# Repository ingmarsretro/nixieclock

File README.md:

# nixieclock
it is a project for a simple nixieclock hardware and software design based on atmega 8bit controller

develpment environment for this project below:
- Arduino IDE 
- Autodesk Eagle schematic and layout tool for pcb design

all files are hosted here in these folders

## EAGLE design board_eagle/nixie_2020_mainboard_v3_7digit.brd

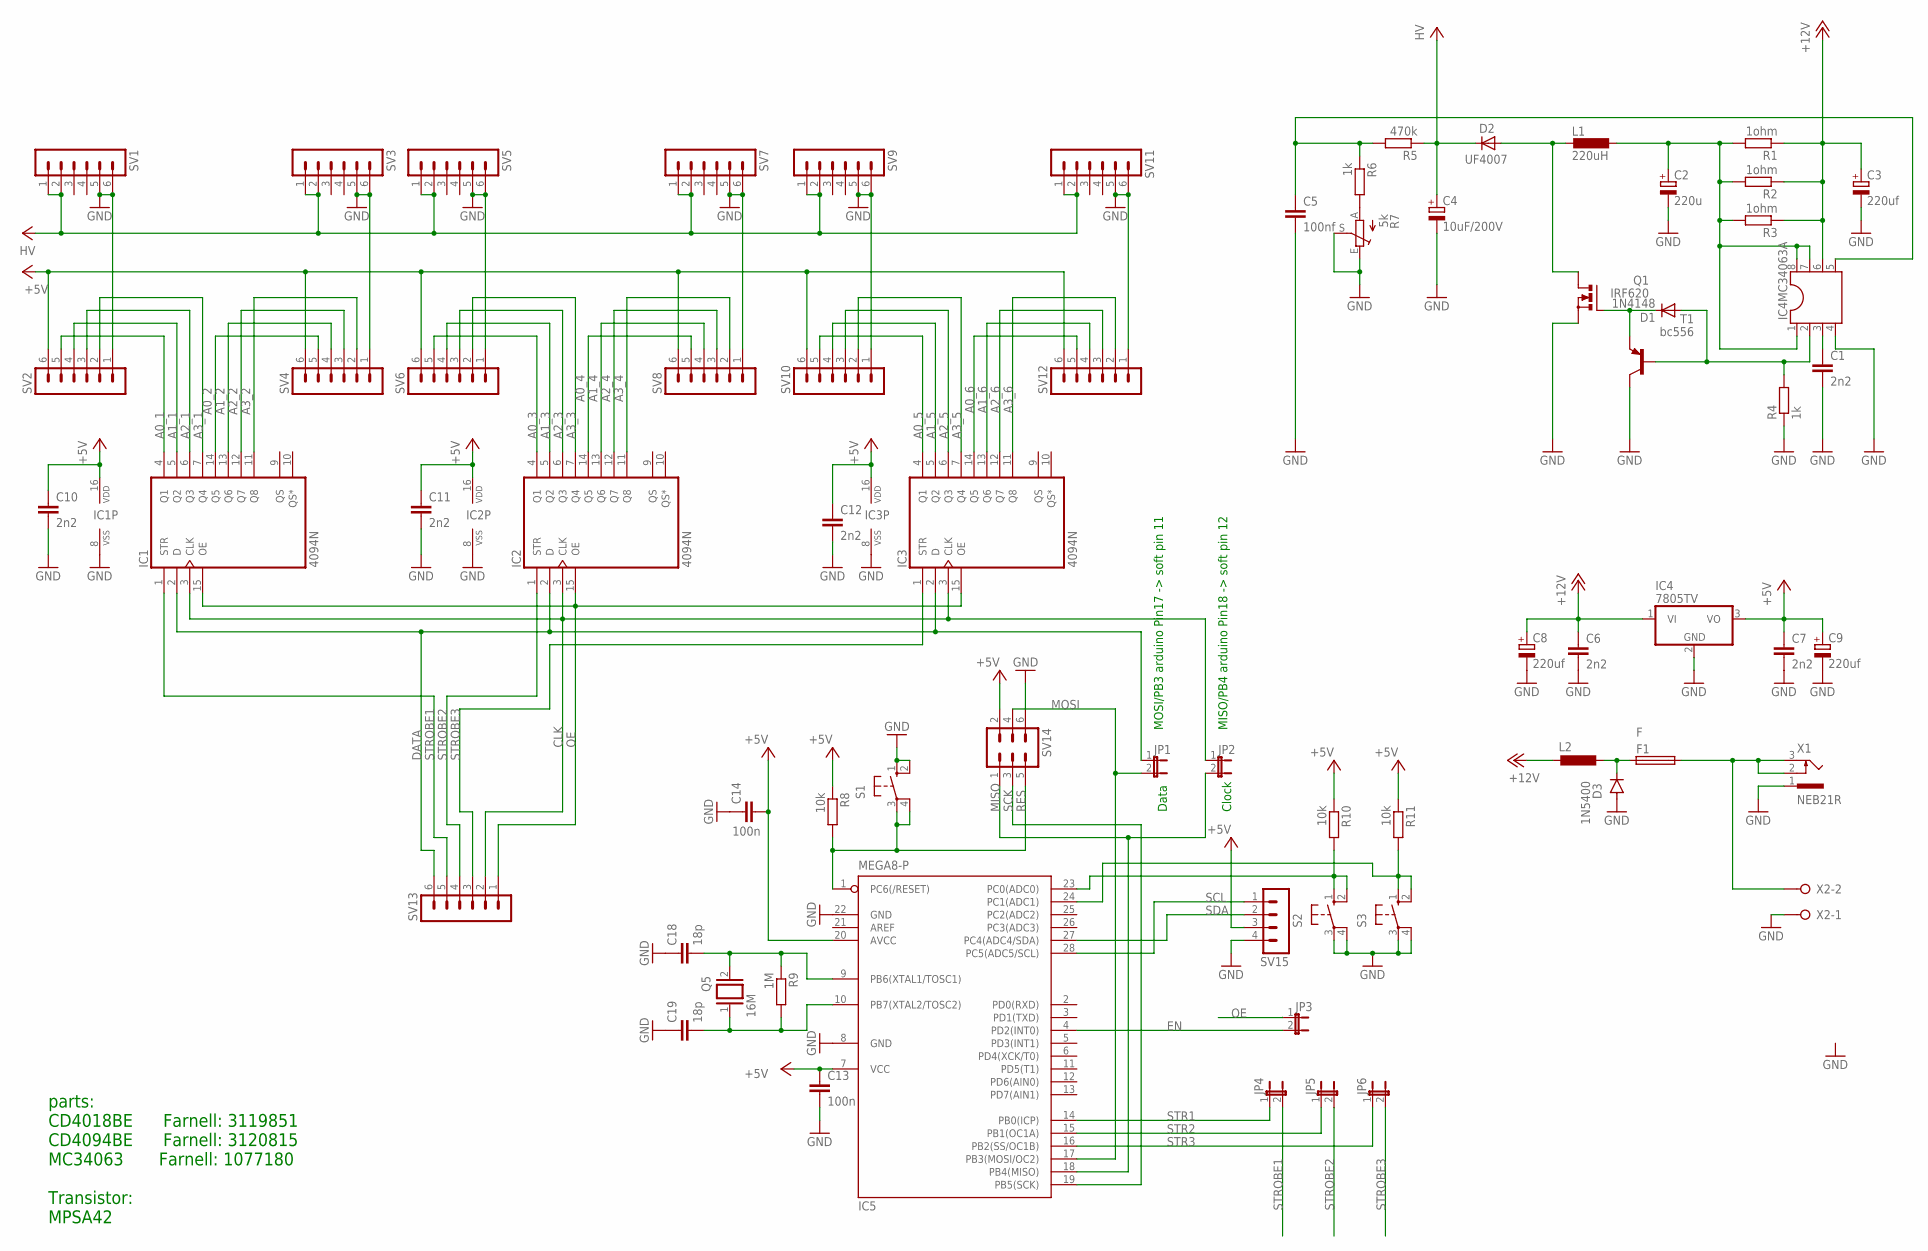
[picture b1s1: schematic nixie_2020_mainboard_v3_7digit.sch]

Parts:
C1, C6, C7, C10, C11, C12: 2n2; C050-030X075
C2: 220u; E5-10,5
C3, C8, C9: 220uf; E5-10,5
C4: 10uF/200V; E5-10,5
C5: 100nf; C075-042X103
C13, C14: 100n; C050-025X075
C18, C19: 18p; C050-025X075
D1: 1N4148; DO35-10
D2: UF4007; DO35-10
D3: 1N5400; DO201-15
F1: F; SHK20L
IC1, IC2, IC3: 4094N; DIL16
IC4: 7805TV; TO220V
IC4MC34063A: DIL8S; SOCKET-08
IC5: MEGA8-P; DIL28-3
JP1, JP2, JP3, JP4, JP5, JP6: JP1E; JP1
L1: 220uH; LAN02KR
L2: L-EU0207/10; 0207/10
Q1: IRF620; TO220BV
Q5: 16M; QS
R1, R2, R3: 1ohm; 0207/12
R4, R6: 1k; 0207/12
R5: 470k; 0207/12
R7: 5k; RJ9W
R8, R10, R11: 10k; 0207/12
R9: 1M; 0207/12
S1, S2, S3: 10-XX; B3F-10XX
SV1, SV2, SV3, SV4, SV5, SV6, SV7, SV8, SV9, SV10, SV11, SV12, SV13: MA06-1
SV14: MA03-2
SV15: MA04-1
T1: bc556; TO92-EBC
X1: NEB21R
X2: W237-02P; W237-132

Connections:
+5V: C7.1, C9.+, C10.1, C11.1, C12.1, C13.1, C14.2, IC1.16 (VDD), IC2.16 (VDD), IC3.16 (VDD), IC4.3 (VO), IC5.7 (VCC), IC5.20 (AVCC), R8.1, R10.1, R11.1, SV2.6, SV4.6, SV6.6, SV8.6, SV10.6, SV12.6, SV14.2, SV15.3
+12V: C3.+, C6.1, C8.+, IC4.1 (VI), IC4MC34063A.6, L2.1, R1.1, R2.1, R3.1
A0_1: IC1.4 (Q1), SV2.5
A0_2: IC1.14 (Q5), SV4.5
A0_3: IC2.4 (Q1), SV6.5
A0_4: IC2.14 (Q5), SV8.5
A0_5: IC3.4 (Q1), SV10.5
A0_6: IC3.14 (Q5), SV12.5
A1_1: IC1.5 (Q2), SV2.4
A1_2: IC1.13 (Q6), SV4.4
A1_3: IC2.5 (Q2), SV6.4
A1_4: IC2.13 (Q6), SV8.4
A1_5: IC3.5 (Q2), SV10.4
A1_6: IC3.13 (Q6), SV12.4
A2_1: IC1.6 (Q3), SV2.3
A2_2: IC1.12 (Q7), SV4.3
A2_3: IC2.6 (Q3), SV6.3
A2_4: IC2.12 (Q7), SV8.3
A2_5: IC3.6 (Q3), SV10.3
A2_6: IC3.12 (Q7), SV12.3
A3_1: IC1.7 (Q4), SV2.2
A3_2: IC1.11 (Q8), SV4.2
A3_3: IC2.7 (Q4), SV6.2
A3_4: IC2.11 (Q8), SV8.2
A3_5: IC3.7 (Q4), SV10.2
A3_6: IC3.11 (Q8), SV12.2
CLK: IC1.3 (CLK), IC2.3 (CLK), IC3.3 (CLK), JP2.1, SV13.2
DATA: IC1.2 (D), IC2.2 (D), IC3.2 (D), JP1.1, SV13.6
EN: IC5.4 (PD2(INT0)), JP3.2
GND: C1.2, C2.-, C3.-, C4.-, C5.2, C6.2, C7.2, C8.-, C9.-, C10.2, C11.2, C12.2, C13.2, C14.1, C18.1, C19.1, D3.A, IC1.8 (VSS), IC2.8 (VSS), IC3.8 (VSS), IC4.2 (GND), IC4MC34063A.4, IC5.8 (GND), IC5.22 (GND), Q1.S, R4.1, R7.E, R7.S, S1.1 (S), S1.2 (S1), S2.3, S2.4 (P1), S3.3, S3.4 (P1), SV1.5, SV1.6, SV2.1, SV3.5, SV3.6, SV4.1, SV5.5, SV5.6, SV6.1, SV7.5, SV7.6, SV8.1, SV9.5, SV9.6, SV10.1, SV11.5, SV11.6, SV12.1, SV14.6, SV15.4, T1.C, X1.1, X2.1
MISO: IC5.18 (PB4(MISO)), JP2.2, SV14.1
MOSI: IC5.17 (PB3(MOSI/OC2)), JP1.2, SV14.4
unnamed: F1.2A (2), X1.2, X1.3, X2.2
unnamed: D3.C, F1.1A (1), L2.2
unnamed: IC5.24 (PC1(ADC1)), R11.2, S3.1 (S), S3.2 (S1)
unnamed: IC5.23 (PC0(ADC0)), R10.2, S2.1 (S), S2.2 (S1)
unnamed: C18.2, IC5.9 (PB6(XTAL1/TOSC1)), Q5.2, R9.1
unnamed: C19.2, IC5.10 (PB7(XTAL2/TOSC2)), Q5.1, R9.2
unnamed: C1.1, IC4MC34063A.3
unnamed: D1.A, IC4MC34063A.2, R4.2, T1.B
unnamed: D1.C, Q1.G, T1.E
unnamed: D2.A, L1.2, Q1.D
unnamed: C2.+, IC4MC34063A.1, IC4MC34063A.7, IC4MC34063A.8, L1.1, R1.2, R2.2, R3.2
unnamed: C5.1, IC4MC34063A.5, R5.2, R6.1
unnamed: R6.2, R7.A
OE: IC1.15 (OE), IC2.15 (OE), IC3.15 (OE), JP3.1, SV13.1
RES: IC5.1 (PC6(/RESET)), R8.2, S1.3, S1.4 (P1), SV14.5
SCK: IC5.19 (PB5(SCK)), SV14.3
SCL: IC5.28 (PC5(ADC5/SCL)), SV15.1
SDA: IC5.27 (PC4(ADC4/SDA)), SV15.2
STR1: IC5.14 (PB0(ICP)), JP4.1
STR2: IC5.15 (PB1(OC1A)), JP5.1
STR3: IC5.16 (PB2(SS/OC1B)), JP6.1
STROBE1: IC1.1 (STR), JP4.2, SV13.5
STROBE2: IC2.1 (STR), JP5.2, SV13.4
STROBE3: IC3.1 (STR), JP6.2, SV13.3
VCC: C4.+, D2.C, R5.1, SV1.1, SV1.2, SV3.1, SV3.2, SV5.1, SV5.2, SV7.1, SV7.2, SV9.1, SV9.2, SV11.1, SV11.2

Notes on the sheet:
MOSI/PB3 arduino Pin17 -> soft pin 11
Data
Clock
MISO/PB4 arduino Pin18 -> soft pin 12
parts: CD4018BE Farnell: 3119851 CD4094BE Farnell: 3120815 MC34063 Farnell: 1077180 Transistor: MPSA42

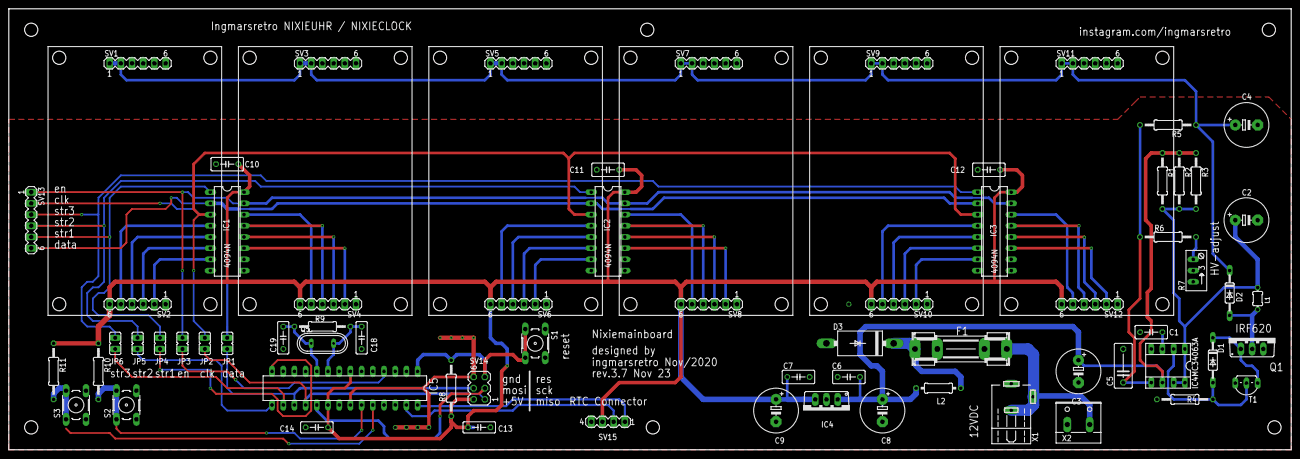
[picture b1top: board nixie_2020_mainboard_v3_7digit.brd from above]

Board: 2 copper layers, 290.8 x 100.0 mm, 68 parts (0 on the bottom side), 57 nets.

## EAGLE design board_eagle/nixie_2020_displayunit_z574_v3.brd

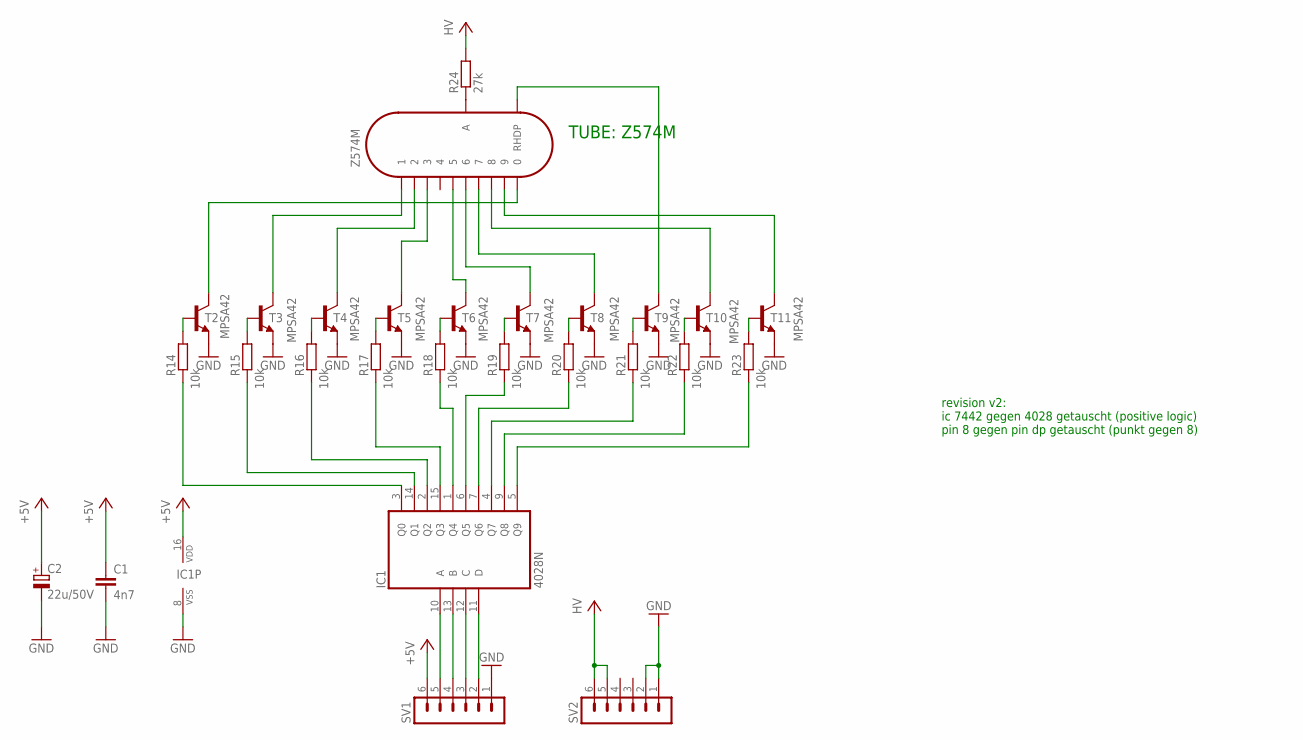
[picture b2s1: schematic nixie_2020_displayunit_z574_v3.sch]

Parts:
C1: 4n7; C075-032X103
C2: 22u/50V; E5-5
IC1: 4028N; DIL16
R14, R15, R16, R17, R18, R19, R20, R21, R22, R23: 10k; 0207/10
R24: 27k; 0207/10
SV1, SV2: MA06-1
T2, T3, T4, T5, T6, T7, T8, T9, T10, T11: MPSA42; TO92-EBC
Z574M: IN-8-2

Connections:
+5V: C1.1, C2.+, IC1.16 (VDD), SV1.6
GND: C1.2, C2.-, IC1.8 (VSS), SV1.1, SV2.1, SV2.2, T2.E, T3.E, T4.E, T5.E, T6.E, T7.E, T8.E, T9.E, T10.E, T11.E
unnamed: IC1.10 (A), SV1.5
unnamed: IC1.13 (B), SV1.4
unnamed: IC1.12 (C), SV1.3
unnamed: IC1.11 (D), SV1.2
unnamed: T9.C, Z574M.. (RHDP)
unnamed: R14.2, T2.B
unnamed: R15.2, T3.B
unnamed: R16.2, T4.B
unnamed: R17.2, T5.B
unnamed: R18.2, T6.B
unnamed: R19.2, T7.B
unnamed: R20.2, T8.B
unnamed: R21.2, T9.B
unnamed: R22.2, T10.B
unnamed: R23.2, T11.B
unnamed: IC1.3 (Q0), R14.1
unnamed: IC1.14 (Q1), R15.1
unnamed: IC1.2 (Q2), R16.1
unnamed: IC1.15 (Q3), R17.1
unnamed: IC1.1 (Q4), R18.1
unnamed: IC1.6 (Q5), R19.1
unnamed: IC1.7 (Q6), R20.1
unnamed: IC1.4 (Q7), R21.1
unnamed: IC1.9 (Q8), R22.1
unnamed: IC1.5 (Q9), R23.1
unnamed: T3.C, Z574M.1
unnamed: T4.C, Z574M.2
unnamed: T5.C, Z574M.3
unnamed: T6.C, Z574M.5
unnamed: T7.C, Z574M.6
unnamed: T8.C, Z574M.7
unnamed: T10.C, Z574M.8
unnamed: T11.C, Z574M.9
unnamed: T2.C, Z574M.0
unnamed: R24.1, Z574M.A
VCC: R24.2, SV2.5, SV2.6

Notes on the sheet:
revision v2: ic 7442 gegen 4028 getauscht (positive logic) pin 8 gegen pin dp getauscht (punkt gegen 8)
TUBE: Z574M

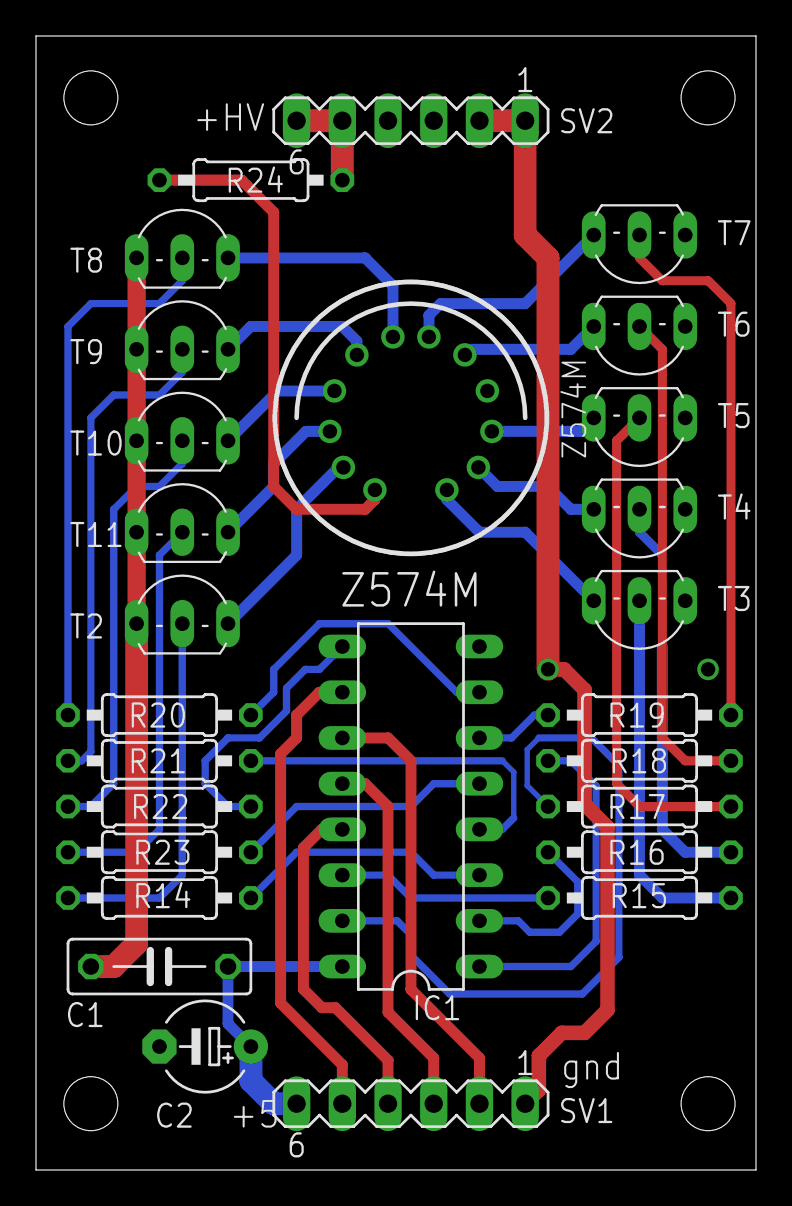
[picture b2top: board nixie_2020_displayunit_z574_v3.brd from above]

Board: 2 copper layers, 40.0 x 63.0 mm, 27 parts (0 on the bottom side), 38 nets.

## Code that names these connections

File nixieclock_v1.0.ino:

 //nixieclock first release v1.0 19.10.2021
 //by ingmarsretro 
 //microcontroller Atmega328
 // der 4094 ist ein 8bit shiftregister
 // je 4 bit davon werden für eine nixieröhre verwendet -> ein bcd zu decimal decoderchip steuert die ziffern an
 // also zeigen je zwei röhren eigentlich hex an (da a-f aber nicht dargestellt wird und die anzeige zur basis 10 anzeigen soll
 // muss das beachtet werden
 
 // ansteuerung der nixies über taktung (pwm)
 // die anzeige an den röhren wird in hex dargestellt -> also der dezimal lesbare anteil der hexcodierung
 
 int countsek = 0;int displ_sek;
 int countmin = 0;int displ_min;  
 int countstd = 0;int displ_hr;  
 int a = 0; int dezs = 0; // -16 daher dass (dezs=dezs+16) und es soll ja bei 0 anfangen und nicht bei 10
 int b = 0; int dezm = 0; //256dec entsr 100 hex also werden 00 angezeigt
 int c = 0; int dezh = 0;  //256dec entsr 100 hex also werden 00 angezeigt 

long myTimer = 0;
long myTimeout = 1000;

    //pinzuordnung für schieberegisteransteuerung 4094
    int str0 = 8;  //Pin connected to STR1(pin 1) of HEF4094
    int str1 = 9;  //Pin connected to STR2(pin 1) of HEF4094
    int str2 = 10; //Pin connected to STR3(pin 1) of HEF4094
    int clk  = 12; //Pin connected to CP  (pin 3) of HEF4094
    int dat = 11; //Pin connected to D   (pin 2) of HEF4094
    int oe = 2;    //pin output enable 

    //eingänge für die bedienung 
    int tasth = A0;
    int tastm = A1; // auch als DDRC = B11111100 pin pc0 und pc1 als input
 
void setup() {
              pinMode(tasth, INPUT); pinMode(tastm, INPUT);  // taster s2 und s3  an PC0(pin23) und PC1(pin24)
              pinMode(str0, OUTPUT); pinMode(str1, OUTPUT); pinMode(str2, OUTPUT);
              pinMode(clk, OUTPUT); pinMode(dat, OUTPUT); pinMode(oe, OUTPUT);
        
              Serial.begin(9600); //   serial debug initialisieren 

              //erstmal alle outputs auf low
              digitalWrite(oe, LOW);
              digitalWrite(str0, LOW); digitalWrite(str1, LOW); digitalWrite(str2, LOW);
              digitalWrite(clk, LOW);
              }



void anzeige(int clk, int displ_sek, int displ_min, int displ_hr) 
              {
              digitalWrite(str0, HIGH);                 //latch HIGH to send data
              shiftOut(dat, clk, MSBFIRST, displ_sek);  //send data
              digitalWrite(str0, LOW);                  //latch LOW to stop sending data
   
              digitalWrite(str1, HIGH);                 //latch HIGH to send data
              shiftOut(dat, clk, MSBFIRST, displ_min);  //send data
              digitalWrite(str1, LOW);                  //latch LOW to stop sending data
              digitalWrite(str2, HIGH);                 //latch HIGH to send data
              shiftOut(dat, clk, MSBFIRST, displ_hr);  //send data
              digitalWrite(str2, LOW);                  //latch LOW to stop sending data 
              delay(5);                  // röhren ein und anzeigen
        
                    // Alle Röhren ohne Anzeige durch Ansteuern von hexAA = 170 dec
                    digitalWrite(str0, HIGH);                 //latch HIGH to send data
                    shiftOut(dat, clk, MSBFIRST, 170); //send data
                    digitalWrite(str0, LOW);                  //latch LOW to stop sending data
                    digitalWrite(str1, HIGH);                 //latch HIGH to send data
                    shiftOut(dat, clk, MSBFIRST, 170); //send data
                    digitalWrite(str1, LOW);                  //latch LOW to stop sending data
                    digitalWrite(str2, HIGH);                 //latch HIGH to send data
                    shiftOut(dat, clk, MSBFIRST, 170); //send data
                    digitalWrite(str2, LOW);                  //latch LOW to stop sending data
                    delay(5);                  // alle röhren aus 
              }

void loop() 
            {
              // Serial.print("\n\r");
              digitalWrite(oe, HIGH); //chip enable für alle ein
       
                    if (digitalRead(A1)== LOW){countmin++;b++;delay(150);}  //minutenwert hochzählen
                    if (digitalRead(A0)== LOW){countstd++;c++;delay(150);} // stundenwert hochzählen

                    if (millis() > myTimeout + myTimer ) {  //sekundentakt erzeugen
                    myTimer = millis();
                    countsek++; a++;
            }
         
              // sekundenzähler     dezimal
                if (a==10) {a=0; dezs=dezs+6;}    
                if (countsek>59) { countsek=0; countmin++; b++; dezs=0;}
         
                          displ_sek=countsek+dezs; 
             // minutenzähler 
               if (b==10) {b=0; dezm=dezm+6;}      
               if (countmin>59) { countmin=0; countstd++; c++; dezm=0;}
         
                          displ_min=countmin+dezm; 
             //stundenzähler    
               if (c==10) {c=0; dezh=dezh+6;}
               if (countstd>23) { countstd=0; dezh=0; c=0;}
                          
                          displ_hr=countstd+dezh; 
         
                 anzeige(clk,displ_sek,displ_min,displ_hr);                     
         
                                Serial.print("\t");
                                Serial.print(countmin); Serial.print("\t");
                                Serial.print(countstd); Serial.print("\t");
                        //      Serial.print(sek_value); Serial.print("\t");
                        //      Serial.print(min_value); Serial.print("\t");
                        //      Serial.print(std_value); 
                                Serial.print("\n\r");
                          }

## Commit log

2023-03-09 Create schematic
2023-10-31 Add files via upload
    this Arduino script works with DS1307 RTC-Clock chip.
    the I2C io´s of the DS1307 must be attached to the ATMEGA pins 28(SCL) and 27(SDA)
2023-10-31 Add files via upload
    updated schematic for use of the DS1307 RTC Board
2023-10-31 Add files via upload
    Updated board and schematic files with RTC connector
